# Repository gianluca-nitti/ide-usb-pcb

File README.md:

Hardware for [ide-usb](https://github.com/gianluca-nitti/ide-usb) project

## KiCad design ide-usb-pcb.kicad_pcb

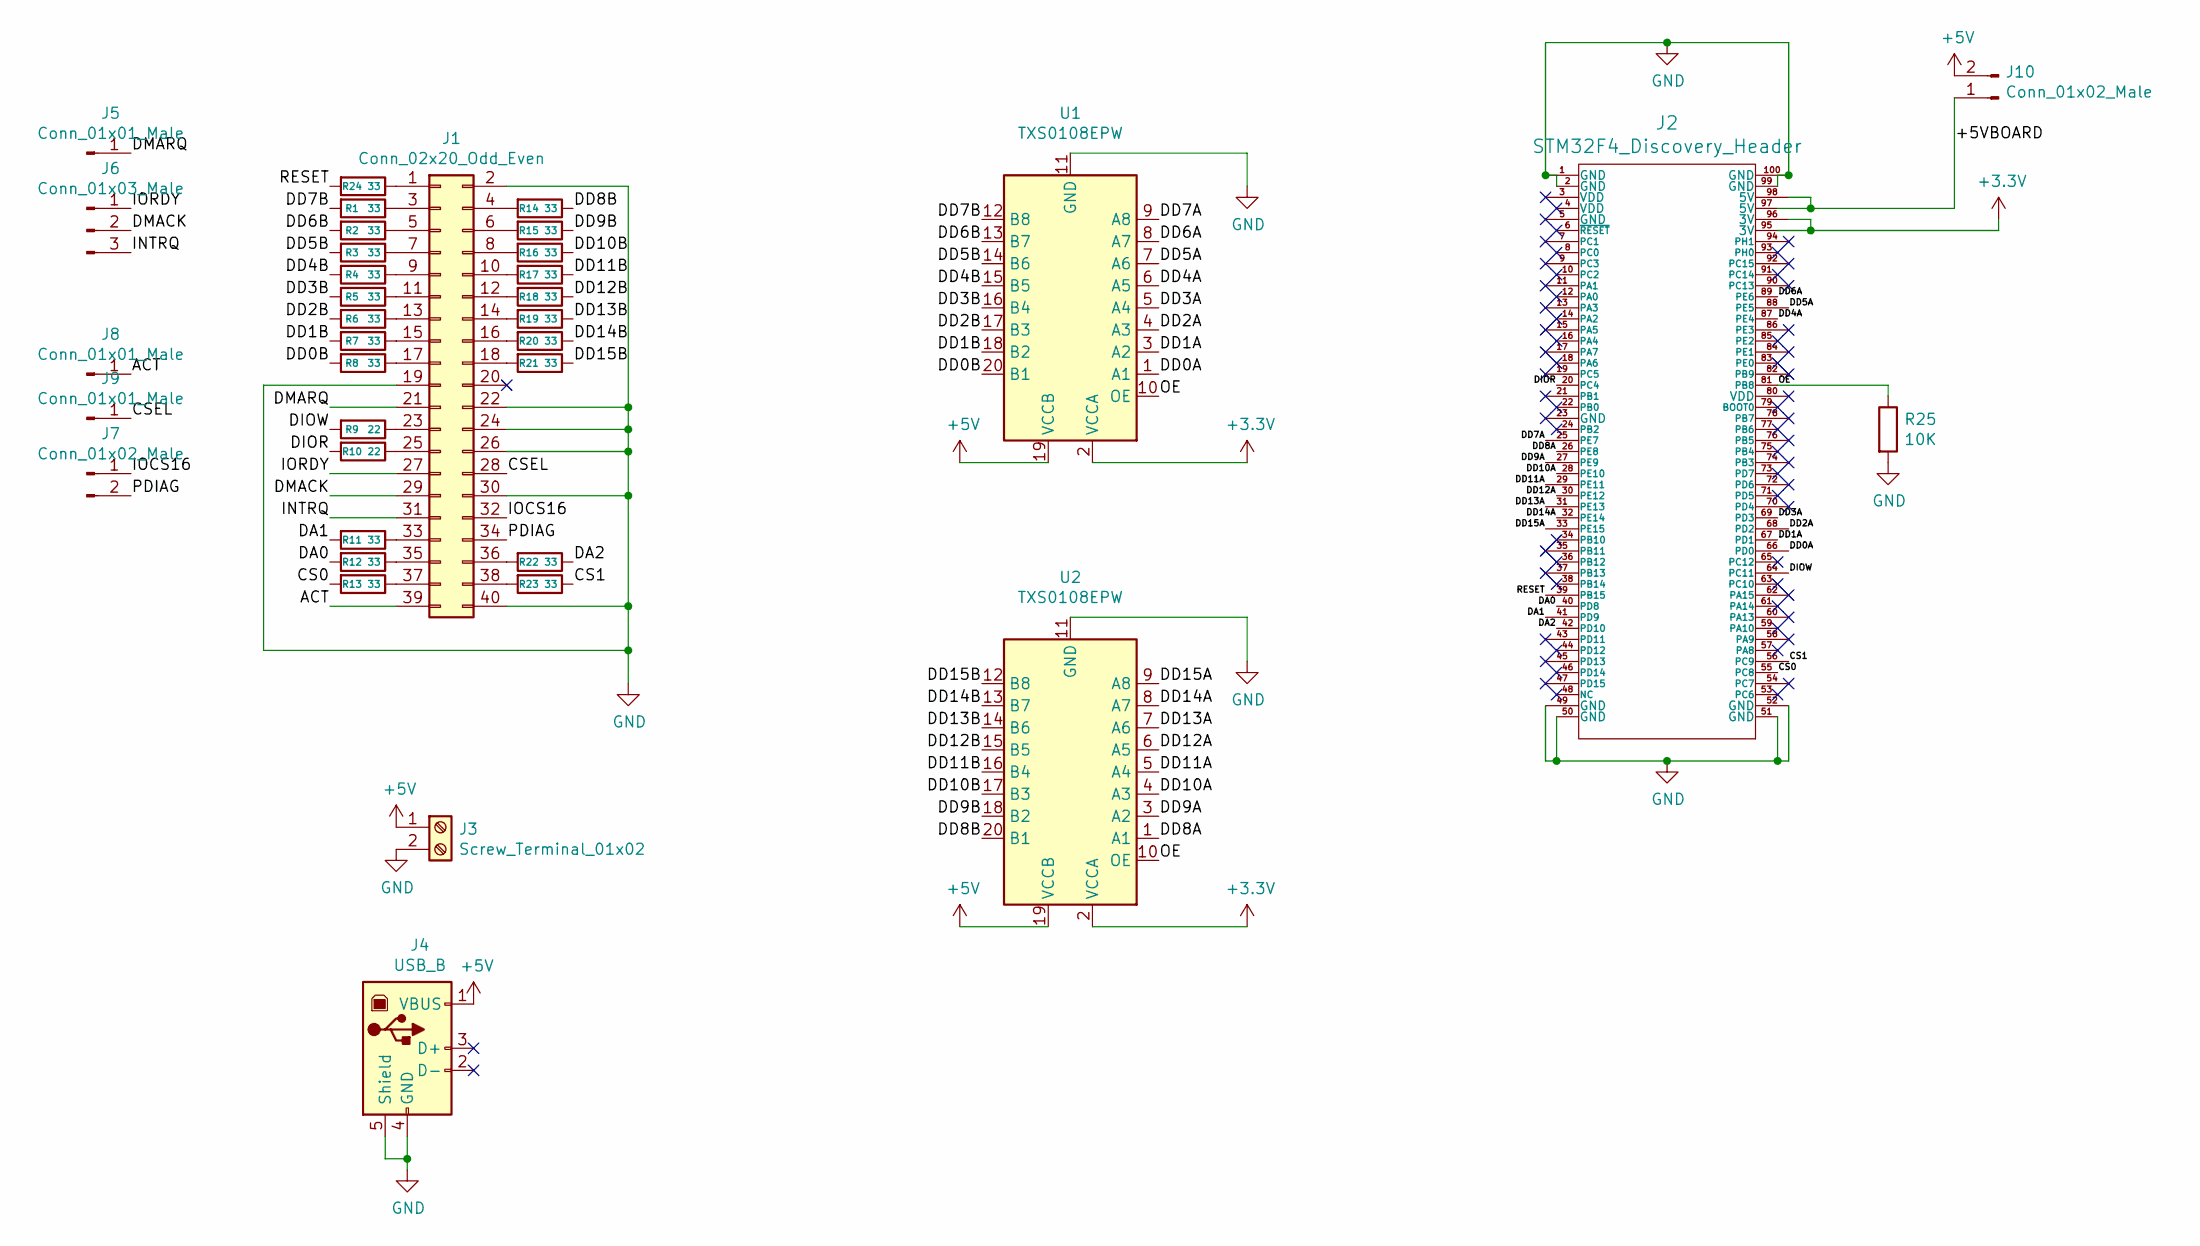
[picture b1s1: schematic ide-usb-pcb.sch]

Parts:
J1: Conn_02x20_Odd_Even; Socket_Strip_Straight_2x20_Pitch2.54mm
J2: STM32F4_Discovery_Header; stm32f4_discovery_header
J3: Screw_Terminal_01x02; TerminalBlock_bornier-2_P5.08mm
J4: USB_B
J5, J8, J9: Conn_01x01_Male; Socket_Strip_Straight_1x01_Pitch2.54mm
J6: Conn_01x03_Male; Socket_Strip_Straight_1x03_Pitch2.54mm
J7, J10: Conn_01x02_Male; Socket_Strip_Straight_1x02_Pitch2.54mm
R1, R2, R3, R4, R5, R6, R7, R8, R11, R12, R13, R14, R15, R16, R17, R18, R19, R20, R21, R22, R23, R24: 33; R_Axial_DIN0204_L3.6mm_D1.6mm_P7.62mm_Horizontal
R9, R10: 22; R_Axial_DIN0204_L3.6mm_D1.6mm_P7.62mm_Horizontal
R25: 10K; R_Axial_DIN0204_L3.6mm_D1.6mm_P7.62mm_Horizontal
U1, U2: TXS0108EPW; TXS0108E_breakout

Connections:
+3V3: J2.95 (3V), J2.96 (3V), U1.2 (VCCA), U2.2 (VCCA)
+5V: J3.1, J4.1 (VBUS), J10.2, U1.19 (VCCB), U2.19 (VCCB)
/+5VBOARD: J2.97 (5V), J2.98 (5V), J10.1
/ACT: J1.39, J8.1
/CS0: J2.55 (PC8), R13.2
/CS1: J2.56 (PC9), R23.1
/CSEL: J1.28, J9.1
/DA0: J2.40 (PD8), R12.2
/DA1: J2.41 (PD9), R11.2
/DA2: J2.42 (PD10), R22.1
/DD0A: J2.66 (PD0), U1.1 (A1)
/DD0B: R8.2, U1.20 (B1)
/DD1A: J2.67 (PD1), U1.3 (A2)
/DD1B: R7.2, U1.18 (B2)
/DD2A: J2.68 (PD2), U1.4 (A3)
/DD2B: R6.2, U1.17 (B3)
/DD3A: J2.69 (PD3), U1.5 (A4)
/DD3B: R5.2, U1.16 (B4)
/DD4A: J2.87 (PE4), U1.6 (A5)
/DD4B: R4.2, U1.15 (B5)
/DD5A: J2.88 (PE5), U1.7 (A6)
/DD5B: R3.2, U1.14 (B6)
/DD6A: J2.89 (PE6), U1.8 (A7)
/DD6B: R2.2, U1.13 (B7)
/DD7A: J2.25 (PE7), U1.9 (A8)
/DD7B: R1.2, U1.12 (B8)
/DD8A: J2.26 (PE8), U2.1 (A1)
/DD8B: R14.1, U2.20 (B1)
/DD9A: J2.27 (PE9), U2.3 (A2)
/DD9B: R15.1, U2.18 (B2)
/DD10A: J2.28 (PE10), U2.4 (A3)
/DD10B: R16.1, U2.17 (B3)
/DD11A: J2.29 (PE11), U2.5 (A4)
/DD11B: R17.1, U2.16 (B4)
/DD12A: J2.30 (PE12), U2.6 (A5)
/DD12B: R18.1, U2.15 (B5)
/DD13A: J2.31 (PE13), U2.7 (A6)
/DD13B: R19.1, U2.14 (B6)
/DD14A: J2.32 (PE14), U2.8 (A7)
/DD14B: R20.1, U2.13 (B7)
/DD15A: J2.33 (PE15), U2.9 (A8)
/DD15B: R21.1, U2.12 (B8)
/DIOR: J2.20 (PC4), R10.2
/DIOW: J2.64 (PC11), R9.2
/DMACK: J1.29, J6.2
/DMARQ: J1.21, J5.1
/INTRQ: J1.31, J6.3
/IOCS16: J1.32, J7.1
/IORDY: J1.27, J6.1
/OE: J2.81 (PB8), R25.1, U1.10 (OE), U2.10 (OE)
/PDIAG: J1.34, J7.2
/RESET: J2.39 (PB15), R24.2
GND: J1.2, J1.19, J1.22, J1.24, J1.26, J1.30, J1.40, J2.1 (GND), J2.2 (GND), J2.49 (GND), J2.50 (GND), J2.51 (GND), J2.52 (GND), J2.99 (GND), J2.100 (GND), J3.2, J4.4 (GND), J4.5 (Shield), R25.2, U1.11 (GND), U2.11 (GND)
unnamed: J1.1, R24.1
unnamed: J1.3, R1.1
unnamed: J1.4, R14.2
unnamed: J1.5, R2.1
unnamed: J1.6, R15.2
unnamed: J1.7, R3.1
unnamed: J1.8, R16.2
unnamed: J1.9, R4.1
unnamed: J1.10, R17.2
unnamed: J1.11, R5.1
unnamed: J1.12, R18.2
unnamed: J1.13, R6.1
unnamed: J1.14, R19.2
unnamed: J1.15, R7.1
unnamed: J1.16, R20.2
unnamed: J1.17, R8.1
unnamed: J1.18, R21.2
unnamed: J1.23, R9.1
unnamed: J1.25, R10.1
unnamed: J1.33, R11.1
unnamed: J1.35, R12.1
unnamed: J1.36, R22.2
unnamed: J1.37, R13.1
unnamed: J1.38, R23.2

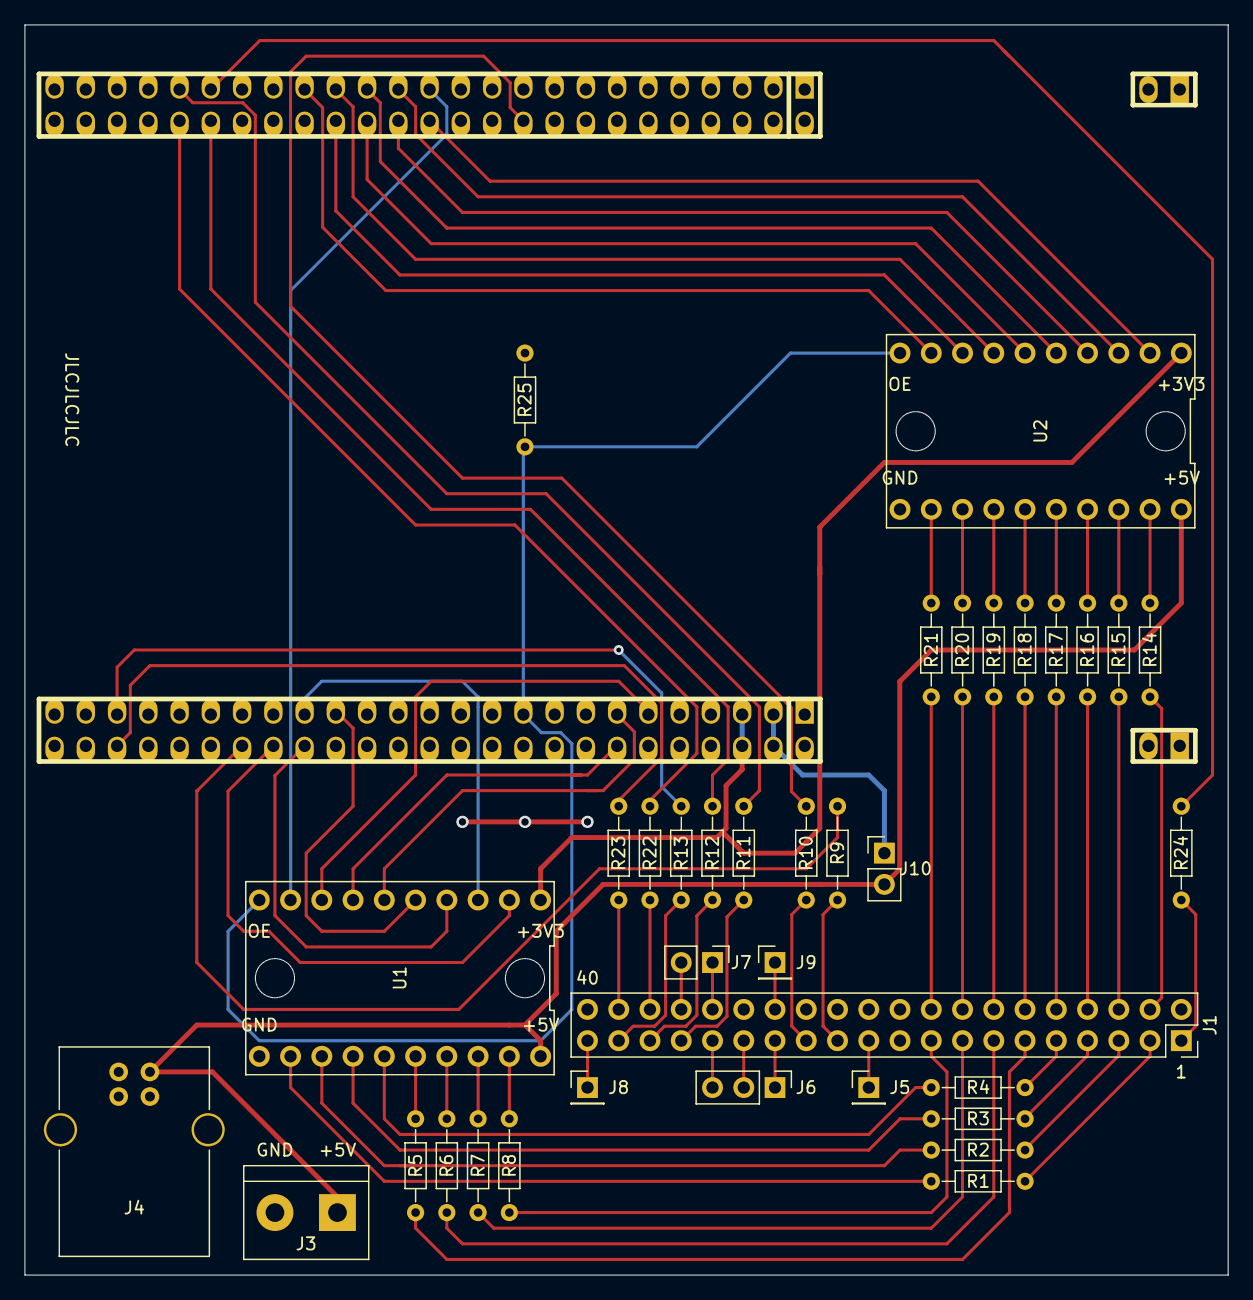
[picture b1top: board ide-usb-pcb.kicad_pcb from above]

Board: 2 copper layers, 97.8 x 101.6 mm, 37 parts (0 on the bottom side), 77 nets.

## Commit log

2021-07-08 Basic components and connections
2021-07-08 Add power & GND nets
2021-07-08 Add termination resistors
2021-07-08 1st attempt at routing, excl ground and power
2021-07-08 New smaller and (maybe) cleaner PCB design
2021-07-08 Add ground plane and route missing traces
2021-07-09 Yet another PCB design
2021-07-09 Fix labels, route more traces
2021-07-09 Add power connectors
2021-07-10 More routing
2021-07-10 First PCB version with everything routed
2021-07-10 Fix terminal block footprint
2021-07-10 Add OE pulldown resistor
2021-07-11 Add level shifter mounting holes
2021-07-11 Improve spacing between some traces
2021-07-11 Add connectors for unused IDE signals
2021-07-12 Add jumper to power STM discovery board
2021-07-12 Improve routing of some traces
    Also improve placement of component names on silkscreen layer
2021-07-12 Minor improvements in component placing and traces
2021-07-12 More small adjustments (silkscreen, move J3 & J4)
2021-07-12 Export Gergebs with JLC guidelines
2021-07-12 Increase hole and pad size for TXS0108E breakout
2021-08-16 Setup schematic plotting
2021-10-08 Add README
